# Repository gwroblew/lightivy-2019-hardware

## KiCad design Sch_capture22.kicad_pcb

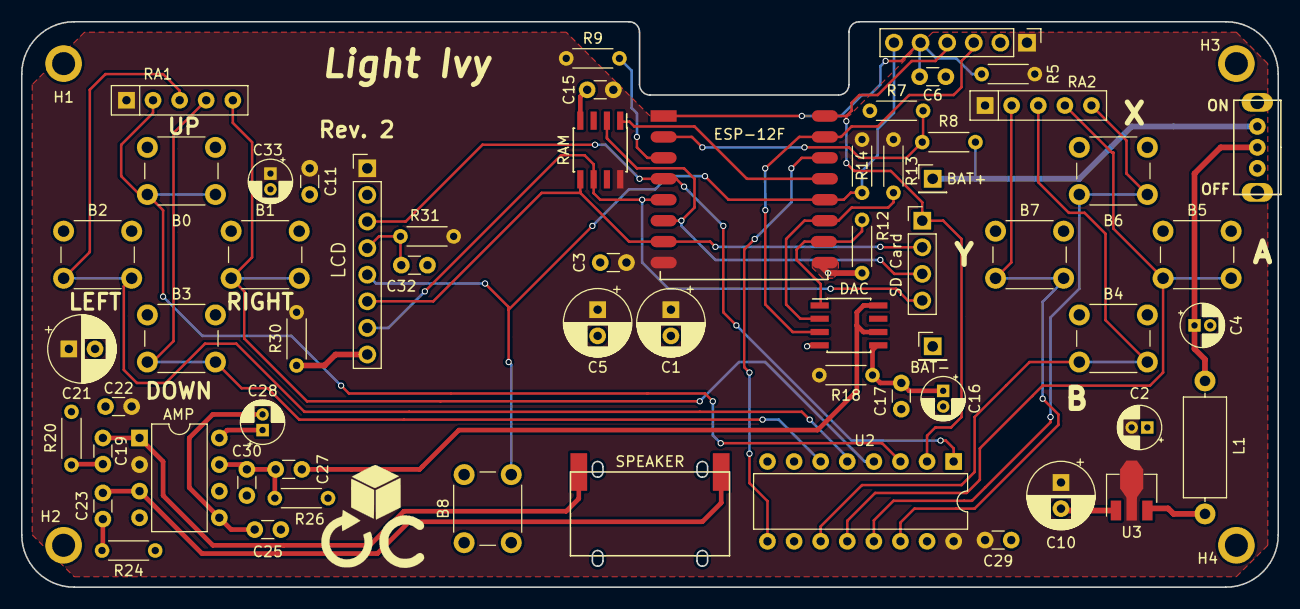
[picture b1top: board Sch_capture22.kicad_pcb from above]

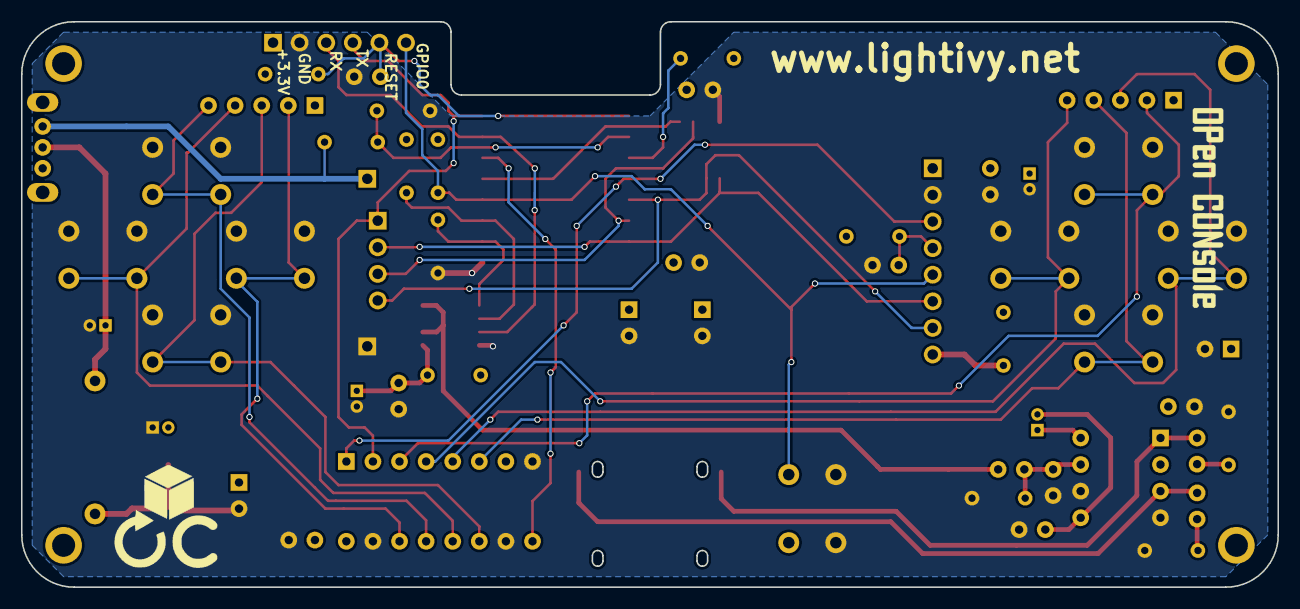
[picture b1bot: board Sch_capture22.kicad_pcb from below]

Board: 2 copper layers, 120.0 x 54.0 mm, 67 parts (2 on the bottom side), 38 nets.

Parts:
AMP: *; DIP-8_W7.62mm
B0, B1, B2, B3, B4, B5, B6, B7, B8: SW_DIP_x01; SW_PUSH_6mm_h5mm
BAT+: Conn_01x01; PinHeader_1x01_P2.54mm_Vertical
BAT-: Conn_01x01; PinHeader_1x01_P2.54mm_Vertical
C1, C5, C10, C21: 220uF; CP_Radial_D6.3mm_P2.50mm
C2, C4, C16, C33: 22uF; CP_Radial_D4.0mm_P1.50mm
C3, C11, C15, C17, C19, C22, C23, C27, C29: 100nF; C_Disc_D3.0mm_W1.6mm_P2.50mm
C6, C32: 1uF; C_Disc_D3.0mm_W1.6mm_P2.50mm
C25: 10nF; C_Disc_D3.0mm_W1.6mm_P2.50mm
C28: 10uF; CP_Radial_D4.0mm_P1.50mm
C30: 22nF; C_Disc_D3.0mm_W1.6mm_P2.50mm
DAC: PT8211-S; SOIC-8_3.9x4.9mm_P1.27mm
ESP-12F: ESP-12F
GR1: LOGO
GR2, GR2#2: LOGO; LOGO2
H1, H2, H3, H4: *; MountingHole_2.2mm_M2_ISO7380_Pad
JP2: Conn_01x06; PinHeader_1x06_P2.54mm_Vertical
L1: 10uH; L_Axial_L9.5mm_D4.0mm_P12.70mm_Horizontal_Fastron_SMCC
LCD: PinHeader_1x08_P2.54mm_Vertical
ON: *; SK12D07VG3
R5, R7, R9, R12, R13, R14, R26, R31: 10k; R_Axial_DIN0204_L3.6mm_D1.6mm_P5.08mm_Horizontal
R8: 30k; R_Axial_DIN0204_L3.6mm_D1.6mm_P5.08mm_Horizontal
R18: 10; R_Axial_DIN0204_L3.6mm_D1.6mm_P5.08mm_Horizontal
R20, R24: 4.7; R_Axial_DIN0204_L3.6mm_D1.6mm_P5.08mm_Horizontal
R30: 18; R_Axial_DIN0204_L3.6mm_D1.6mm_P5.08mm_Horizontal
RA1, RA2: R_Network04; R_Array_SIP5
RAM: VTI7064MSME; SOIC-8_3.9x4.9mm_P1.27mm
SD Card: PinHeader_1x04_P2.54mm_Vertical
SPEAKER: Speaker; Speaker_7417Q
U2: 74HC165; DIP-16_W7.62mm
U3: QX2304LXXE; SOT-89-3

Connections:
AMP-1: AMP.1, C19.1, SPEAKER.2
AMP-3: AMP.3, C23.1, SPEAKER.1
AMP-5: AMP.5, C25.2, C28.2
AMP-7: AMP.7, C27.1, C30.1, R26.2
AMP-8: AMP.8, C28.1
AMP-C100nF19-2: C19.2, R20.2
AMP-C100nF23-2: C23.2, R24.2
DAC-6: C27.2, DAC.6, DAC.8
GND: AMP.4, AMP.6, B0.1, B1.1, B2.1, B3.1, B4.1, B5.1, B6.1, B7.1, B8.1, BAT-.1, C1.2, C2.1, C3.1, C4.2, C5.2, C6.1, C10.2, C11.1, C15.1, C16.2, C17.1, C21.2, C22.1, C25.1, C29.1, C30.2, C32.1, C33.2, DAC.4, ESP-12F.9, JP2.2, LCD.2, R7.1, R12.1, R20.1, R24.1, R26.1, RAM.4, U2.8, U2.10, U2.15, U3.1
L1-2: C4.1, L1.2, ON.2
LCD-4: LCD.8, R30.2
LCD-6: C32.2, LCD.4, R31.2
SW1-3: BAT+.1, ON.3, R8.2
U1-1: C6.2, ESP-12F.1, JP2.5, R5.2
U1-2: ESP-12F.2, R7.2, R8.1
U1-3: ESP-12F.3, R9.2
U1-4: ESP-12F.4, LCD.3, U2.1
U1-5: ESP-12F.5, LCD.7, RAM.6, SD Card.4
U1-6: ESP-12F.6, RAM.2, SD Card.3
U1-7: ESP-12F.7, LCD.6, RAM.5, SD Card.2
U1-10: DAC.1, ESP-12F.10, R12.2
U1-11: DAC.2, ESP-12F.11, R13.2
U1-12: B8.2, ESP-12F.12, JP2.6, LCD.5, R14.2
U1-13: ESP-12F.13, RAM.1
U1-14: ESP-12F.14, U2.9
U1-15: DAC.3, ESP-12F.15, JP2.3
U1-16: ESP-12F.16, JP2.4, SD Card.1, U2.2
U2-3: B0.2, RA1.2, U2.3
U2-4: B1.2, RA1.5, U2.4
U2-5: B2.2, RA1.3, U2.5
U2-6: B3.2, RA1.4, U2.6
U2-11: B4.2, RA2.3, U2.11
U2-12: B5.2, RA2.4, U2.12
U2-13: B6.2, RA2.5, U2.13
U2-14: B7.2, RA2.2, U2.14
U3-3: L1.1, U3.3
VCC: AMP.2, C1.1, C2.2, C3.2, C5.1, C10.1, C11.2, C15.2, C21.1, C22.2, C29.2, C33.1, ESP-12F.8, JP2.1, LCD.1, R5.1, R9.1, R13.1, R14.1, R18.2, R30.1, R31.1, RA1.1, RA2.1, RAM.8, U2.16, U3.2
VDD: C16.1, C17.2, DAC.5, R18.1

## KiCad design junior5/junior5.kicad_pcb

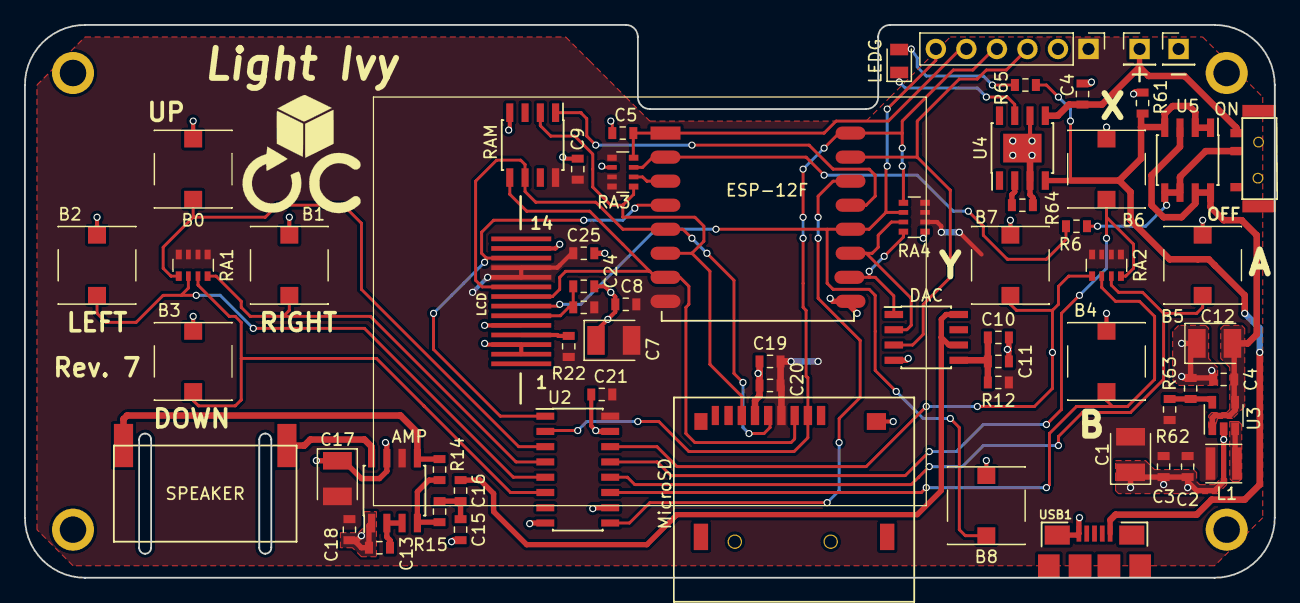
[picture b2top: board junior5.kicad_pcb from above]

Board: 2 copper layers, 104.0 x 46.0 mm, 70 parts (1 on the bottom side), 42 nets.

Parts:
+: Conn_01x01; PinHeader_1x01_P2.54mm_Vertical
-: Conn_01x01; PinHeader_1x01_P2.54mm_Vertical
AMP: FM8002A; SOIC-8_3.9x4.9mm_P1.27mm
B0, B1, B2, B3, B4, B5, B6, B7, B8: SW_DIP_x01; SOFT_BUTTON_6x6mm.kicad_mod
C1, C7, C12, C17: 220uF; CP_EIA-3528-21_Kemet-B
C2, C4, C4#2, C10, C19, C25: 22uF; C_0603_1608Metric
C3, C8, C9, C11, C15, C16, C18, C20, C21: 100nF; C_0603_1608Metric
C5, C13, C24: 1uF; C_0603_1608Metric
DAC: PT8211-S; SOIC-8_3.9x4.9mm_P1.27mm
ESP-12F: ESP-12F
GR1: LOGO
GR2: LOGO; LOGO2
H1, H2, H3, H4: *; MountingHole_2.2mm_M2_ISO7380_Pad
JP2: Conn_01x06; PinHeader_1x06_P2.54mm_Vertical
L1: 2.2uH; L_Taiyo-Yuden_MD-3030
LCD: LCD_TFT177F254
LEDG: GREEN; LED_0805_2012Metric
MicroSD: Micro_SD_Card_Det; MicroSD_TFP-09-2-12B
ON: *; MSK12C02
R6, R14: 30k; R_0603_1608Metric
R12: 10; R_0603_1608Metric
R15: 20k; R_0603_1608Metric
R22: 18; R_0603_1608Metric
R23: 10k; R_0603_1608Metric
R61: 1M; R_0603_1608Metric
R62: 453k; R_0603_1608Metric
R63: 100k; R_0603_1608Metric
R64, R65: 2k; R_0603_1608Metric
RA1, RA2, RA3, RA4: 10k; R_Array_Convex_4x0603
RAM: VTI7064MSME; SOIC-8_3.9x4.9mm_P1.27mm
SPEAKER: Speaker; Speaker_7417Q
U2: 74HC165; SOIC-16_3.9x9.9mm_P1.27mm
U3: SY8008B; SOT-23-5
U4: XT2052; HTSOP-8-1EP_3.9x4.9mm_P1.27mm
U5: DMS2085LSD; SOIC-8_3.9x4.9mm_P1.27mm
USB1: USB_B_Micro; USB-MICRO-B-FCI-10118192

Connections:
AMP-2: AMP.2, AMP.3, C13.2
AMP-4: AMP.4, R14.1, R15.1
AMP-5: AMP.5, R14.2, SPEAKER.2
AMP-8: AMP.8, SPEAKER.1
AMP-R15-2: C15.1, C16.1, R15.2
DAC-6: C16.2, DAC.6, DAC.8
GND: -.1, AMP.1, AMP.7, B0.1, B1.1, B2.1, B3.1, B4.1, B5.1, B6.1, B7.1, B8.1, C1.1, C2.1, C3.1, C4.1, C4#2.1, C5.1, C7.1, C8.1, C9.1, C10.1, C11.1, C12.1, C13.1, C15.2, C17.1, C18.1, C19.1, C20.1, C21.1, C24.1, C25.1, DAC.4, ESP-12F.9, JP2.2, LCD.2, LCD.3, LCD.5, LCD.13, MicroSD.6, MicroSD.12, R61.2, R63.2, R64.2, RA3.2, RA4.1, RAM.4, U2.8, U2.10, U2.15, U3.2, U4.3, U4.6, U4.9, USB1.1, USB1.6
LCD-4: LCD.4, R22.2
LCD-6: C24.2, LCD.6, R23.2
SW1-3: +.1, C4#2.2, ON.3, U4.5
U1-1: C5.2, ESP-12F.1, JP2.5, RA3.8
U1-2: ESP-12F.2, R6.1, RA3.7
U1-3: ESP-12F.3, RA3.6
U1-4: ESP-12F.4, LCD.12, U2.1
U1-5: ESP-12F.5, LCD.9, MicroSD.5, RAM.6
U1-6: ESP-12F.6, MicroSD.7, RA3.5, RAM.2
U1-7: ESP-12F.7, LCD.8, MicroSD.3, RAM.5
U1-10: DAC.1, ESP-12F.10, RA4.8
U1-11: DAC.2, ESP-12F.11, RA4.7
U1-12: B8.2, ESP-12F.12, JP2.6, LCD.7, RA4.6
U1-13: ESP-12F.13, RAM.1
U1-14: ESP-12F.14, U2.9
U1-15: DAC.3, ESP-12F.15, JP2.3
U1-16: ESP-12F.16, JP2.4, MicroSD.2, RA4.5, U2.2
U2-3: B0.2, RA1.5, U2.3
U2-4: B1.2, RA1.8, U2.4
U2-5: B2.2, RA1.6, U2.5
U2-6: B3.2, RA1.7, U2.6
U2-11: B4.2, RA2.6, U2.11
U2-12: B5.2, RA2.7, U2.12
U2-13: B6.2, RA2.8, U2.13
U2-14: B7.2, RA2.5, U2.14
U3-3: L1.1, U3.3
U3-4: C4.2, C12.2, U3.1, U3.4, U5.3, U5.7, U5.8
U3-5: R62.1, R63.1, U3.5
U4-2: R64.1, U4.2
U4-7: LEDG.1, U4.7
U4-LEDR-2: LEDG.2, R65.1
U5-5: ON.2, R6.2, U5.5, U5.6
USB1-1: R61.1, R65.2, U4.4, U5.1, U5.2, U5.4, USB1.5
VCC: AMP.6, C1.2, C2.2, C3.2, C7.2, C8.2, C9.2, C17.2, C18.2, C19.2, C20.2, C21.2, C25.2, ESP-12F.8, JP2.1, L1.2, LCD.10, LCD.11, MicroSD.4, R12.1, R22.1, R23.1, R62.2, RA1.1, RA1.2, RA1.3, RA1.4, RA2.1, RA2.2, RA2.3, RA2.4, RA3.1, RA3.3, RA3.4, RA4.2, RA4.3, RA4.4, RAM.8, U2.16
VDD: C10.2, C11.2, DAC.5, R12.2
